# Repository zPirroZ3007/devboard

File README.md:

# STM32 Devboard

This is my first serious PCB designed for manufacturing.  
It's a microcontroller development board based on the **STM32F411CEU6**.

---

## 🎯 Project Goals

- [x] Learn basics of schematic organization
- [x] Learn basics of PCB routing and component placement
- [x] Get familiar with PCBWay and Chinese manufacturing
- [x] Achieve plug-and-play support in Arduino IDE via USB-C
- [x] Small form factor, **breadboard-friendly**

---

## 📷 Project Media

<p align="center">
  
  <br/><br/>
  
  <br/><br/>
  
</p>

---

## 🧩 MCU Specs (STM32F411CEU6)

- ARM Cortex-M4 @ 100 MHz
- 512 KB Flash, 128 KB SRAM
- USB OTG
- SPI / I2C / UART
- ADC / TIM / DMA

---

## 🛠 Toolchain

- **ECAD:** KiCad
- **Manufacturing:** PCBWay
- **Firmware:** Arduino IDE / STM32 Core
- **Debugging:** SWD

---

## 📦 Status

Power-up tests were successful: power rails are within expected ranges and no shorts were observed. Next step is flashing the initial firmware via ST-Link.

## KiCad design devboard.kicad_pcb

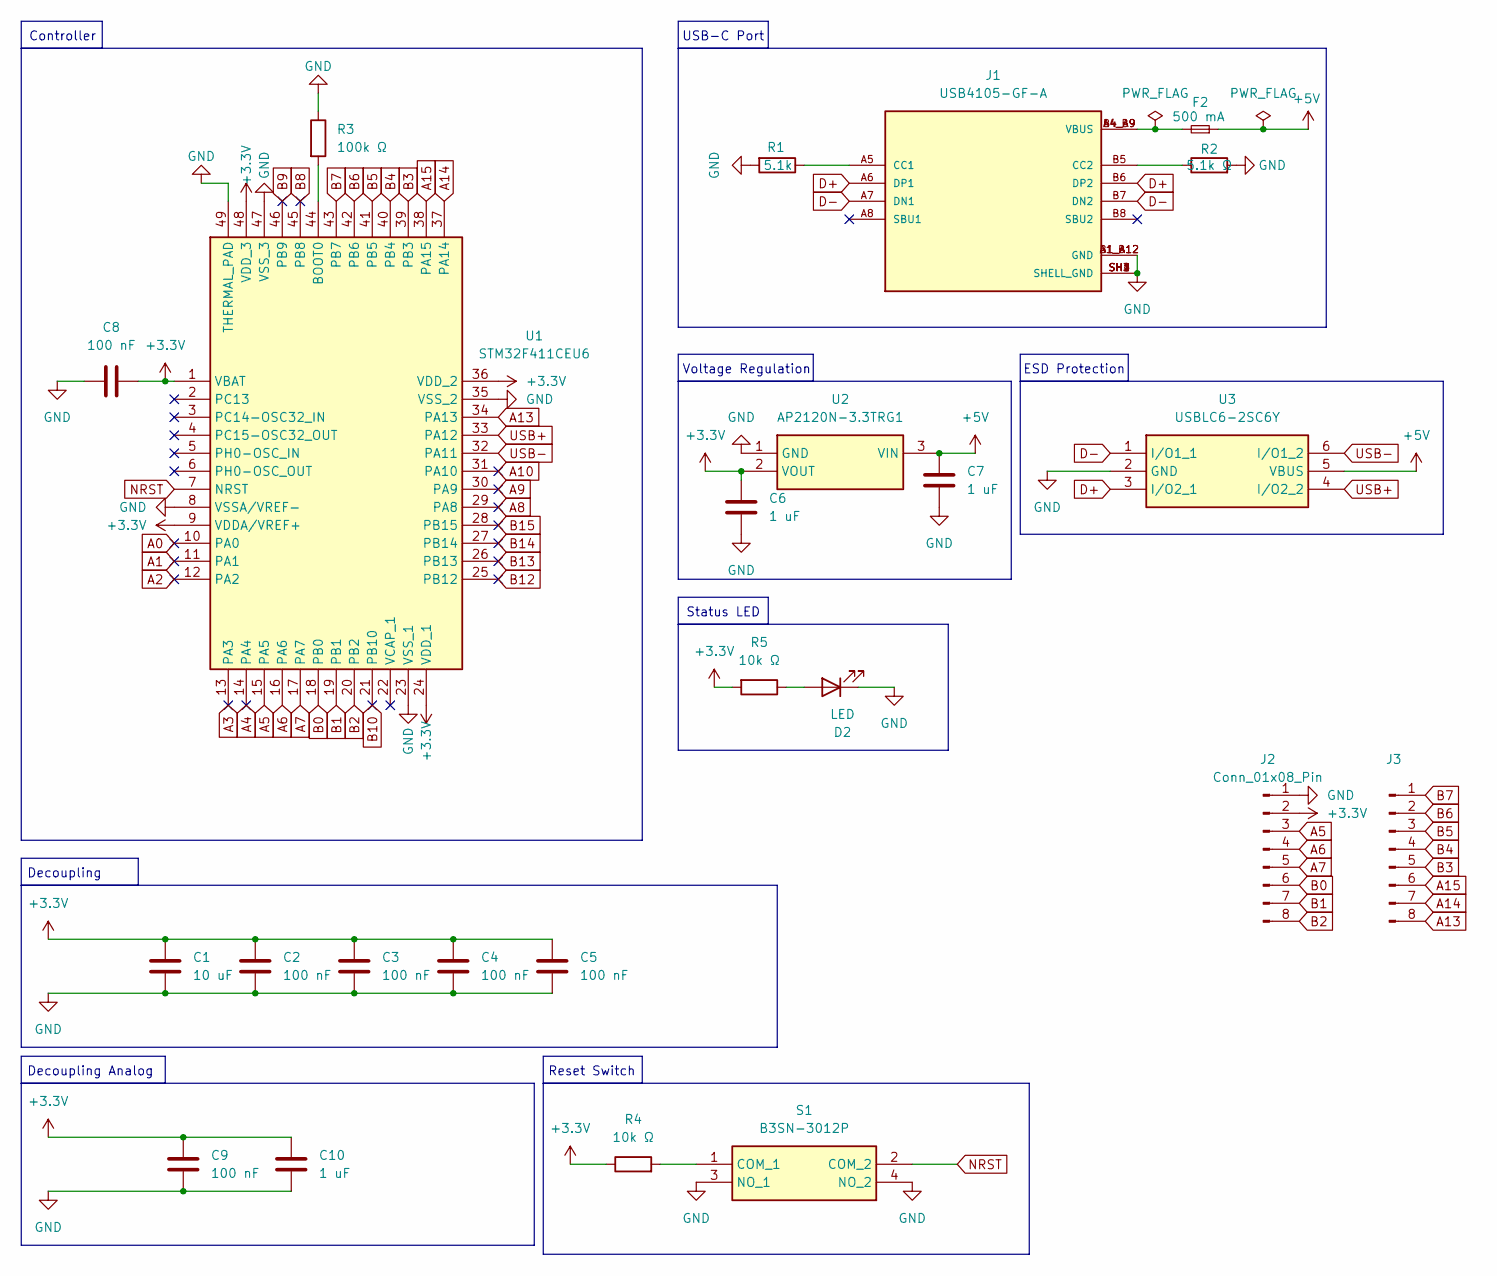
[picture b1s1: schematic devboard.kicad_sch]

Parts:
C1: 10 uF; C_0402_1005Metric
C2, C3, C4, C5, C9: 100 nF; C_0402_1005Metric
C6, C7: 1 uF; C_0603_1608Metric
C8: 100 nF; C_0603_1608Metric
C10: 1 uF; C_0402_1005Metric
D2: LED; LED_0603_1608Metric
F2: 500 mA; Fuse_0603_1608Metric
J1: USB4105-GF-A; GCT_USB4105-GF-A; PARTREV B4
J2, J3: Conn_01x08_Pin; PinHeader_1x08_P2.54mm_Vertical
R1: 5.1k; R_0603_1608Metric
R2: 5.1k Ω; R_0603_1608Metric
R3: 100k Ω; R_0603_1608Metric
R4, R5: 10k Ω; R_0603_1608Metric
S1: B3SN-3012P; B3SN3012P; Mouser Part Number 653-B3SN-3012P
U1: STM32F411CEU6; QFN50P700X700X60-49N-D; Mouser Part Number 511-STM32F411CEU6
U2: AP2120N-3.3TRG1; SOT96P240X105-3N; Mouser Part Number 621-AP2120N-3.3TRG1
U3: USBLC6-2SC6Y; SOT95P280X145-6N; Mouser Part Number 511-USBLC6-2SC6Y

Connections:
+3.3V: C1.1, C2.1, C3.1, C4.1, C5.1, C6.1, C8.2, C9.1, C10.1, J2.2, R4.1, R5.2, U1.1 (VBAT), U1.9 (VDDA/VREF+), U1.24 (VDD_1), U1.36 (VDD_2), U1.48 (VDD_3), U2.2 (VOUT)
+5V: C7.1, F2.1, U2.3 (VIN), U3.5 (VBUS)
A0: U1.10 (PA0)
A1: U1.11 (PA1)
A2: U1.12 (PA2)
A3: U1.13 (PA3)
A4: U1.14 (PA4)
A5: J2.3, U1.15 (PA5)
A6: J2.4, U1.16 (PA6)
A7: J2.5, U1.17 (PA7)
A8: U1.29 (PA8)
A9: U1.30 (PA9)
A10: U1.31 (PA10)
A13: J3.8, U1.34 (PA13)
A14: J3.7, U1.37 (PA14)
A15: J3.6, U1.38 (PA15)
B0: J2.6, U1.18 (PB0)
B1: J2.7, U1.19 (PB1)
B2: J2.8, U1.20 (PB2)
B3: J3.5, U1.39 (PB3)
B4: J3.4, U1.40 (PB4)
B5: J3.3, U1.41 (PB5)
B6: J3.2, U1.42 (PB6)
B7: J3.1, U1.43 (PB7)
B8: U1.45 (PB8)
B9: U1.46 (PB9)
B10: U1.21 (PB10)
B12: U1.25 (PB12)
B13: U1.26 (PB13)
B14: U1.27 (PB14)
B15: U1.28 (PB15)
D+: J1.A6 (DP1), J1.B6 (DP2), U3.3 (I/O2_1)
D-: J1.A7 (DN1), J1.B7 (DN2), U3.1 (I/O1_1)
GND: C1.2, C2.2, C3.2, C4.2, C5.2, C6.2, C7.2, C8.1, C9.2, C10.2, D2.1 (K), J1.A1_B12 (GND), J1.B1_A12 (GND), J1.SH1 (SHELL_GND), J1.SH2 (SHELL_GND), J1.SH3 (SHELL_GND), J1.SH4 (SHELL_GND), J2.1, R1.2, R2.2, R3.1, S1.3 (NO_1), S1.4 (NO_2), U1.8 (VSSA/VREF-), U1.23 (VSS_1), U1.35 (VSS_2), U1.47 (VSS_3), U1.49 (THERMAL_PAD), U2.1 (GND), U3.2 (GND)
NRST: S1.2 (COM_2), U1.7 (NRST)
unnamed: D2.2 (A), R5.1
unnamed: F2.2, J1.A4_B9 (VBUS), J1.B4_A9 (VBUS)
unnamed: J1.A5 (CC1), R1.1
unnamed: J1.B5 (CC2), R2.1
unnamed: R4.2, S1.1 (COM_1)
unnamed: R3.2, U1.44 (BOOT0)
USB+: U1.33 (PA12), U3.4 (I/O2_2)
USB-: U1.32 (PA11), U3.6 (I/O1_2)

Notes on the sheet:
USB-C Port
Decoupling
Status LED
ESD Protection
Decoupling Analog
Controller
Reset Switch
Voltage Regulation

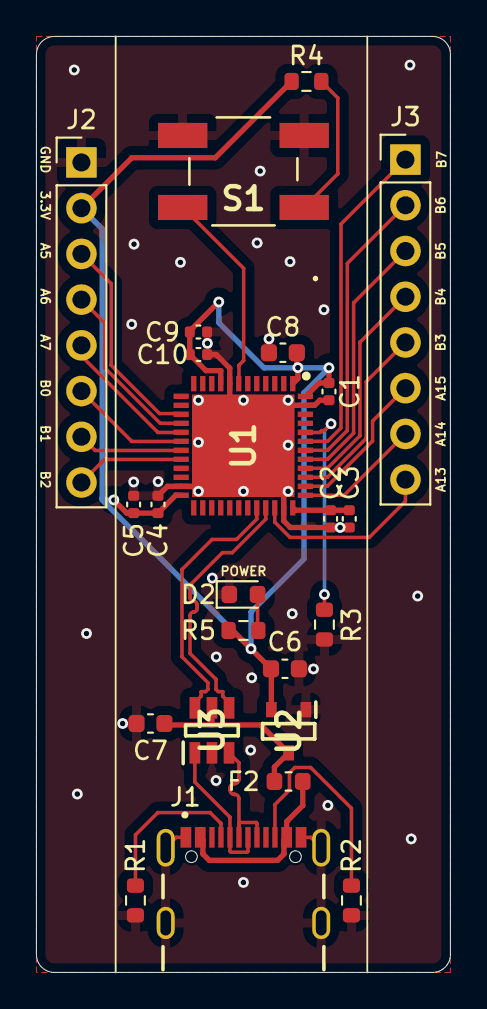
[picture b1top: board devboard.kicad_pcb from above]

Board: 2 copper layers, 23.0 x 52.0 mm, 24 parts (0 on the bottom side), 28 nets.

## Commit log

2025-10-28 Init
2025-12-16 Total board refactoring: - Full board routing - Ready for manufacturing - Schematic fixing ad improvements
2025-12-16 Fixed all DRC errors
2025-12-16 Default clearance fixed 0.15mm
2025-12-16 Fixed serigraphy
2025-12-16 Ground connections fixes
2025-12-16 Fixed ALL DRC and unconnected errors
2025-12-16 Fixes
2025-12-17 Fix VBAT
2026-01-11 Increase PWR LED resistence value + better silkscreen placement
2026-01-11 README images
2026-01-11 README
2026-01-11 remove gif
2026-01-13 Expose A13 to work with ST-Link
2026-01-23 Enhance README with media and video embed
    Added YouTube video embed and project media images to README.
2026-01-23 Update YouTube video embed to thumbnail link
    Replaced YouTube iframe with a clickable thumbnail link.
2026-01-23 Update YouTube video thumbnail link format
2026-01-23 Change YouTube video link thumbnail
    Updated YouTube video thumbnail in README.
